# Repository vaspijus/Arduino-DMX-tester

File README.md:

DMX signal tester tool

Projekto paskirtis – daryti pirminį testavimą DMX signalais valdomiems prietaisams, bei 3pin DMX laidams. Projektą sudarys du atskiri prietaisai sudėti į vieną dėžutę.
1.	Prožektorių testavimo prietaisas skirtas patikrinti ar visi prietaiso kanalai yra veikiantys. Testavimo scenarijus: įjungus apšvietimo prožektorių bus prijungiamas  DMX testeris ir trijų mygtukų pagalba bus įvedamas pradinis prietaiso adresas (pirmas mygtukas bus skirtas šimtams ir turės vertes nuo 0 iki 5,antras mygtukas skirtas dešimtims ir turės vertes nuo 0 iki 9, trečias mygtukas skirtas vienetams turės vertes nuo 0 iki 9. Vertė padidės vienetu paspaudus mygtuką.), tuomet ketvituoju mygtuku (enter) bus paleidžiamas testavimas. Testuojami bus 4 sekantys kanalai nuo to, kuris buvi įvestas. Testeris pirmiausiai pereis per visus 4 kanalus po vieną atskirai didindamas vertes nuo 0 iki 255 paskui kanalai bus įvedami poromis taip pat nuo 0 iki 255 vertės. Toks testavimas vyks iki kol enter mygtukas bus nuspaustas dar kartą arba įvestas naujas kanalo adresas. Kanalų adresai bei dabartinė testerio būsena (On Test, On Hold) bus matoma OLED ekrane. Sistemos maitinimui bus naudojama 9V baterija, įjungimui bus naudojamas dar viengas jungiklis (mygtukas), kuris įjungs abi sistemas vienu kartu (Prožektorių testerį bei DMX laidų testerį).
Reikalingų detalių sąrašas:
Arduino UNO x1
DMX shield x1
LED screen x1
Buttons x4 
9V batery x1 (same for both testers)
9 volts battery connector x1 (same for both testers)
Switch x1 
Connecting wires 
2.	Antra projekto dalis – DMX (3pin) laidų testavimo prietaisas. Šis prietaisas testuos ar signalas praeina per DMX laidą (atskiras laido gyslas). Tam bus naudojamas vienas mygtukas, kuris įjungs/išjungs testavimą. Prijungus DMX laidą ir paleidus testavimą iš 3 digital output pinų bus siunčiami signalai į 3 digital input ir tikrinama ar signalas buvo gautas.
Testavimo logika žingsniais:
1 – patikrinamas kiekvienas pin atskirai (įjungiamas pin 1 sekundei ir pereinama prie senakčio pin taip paraktojami 3 ratai).
2 – Ijungiami visi trys pin vienu kartu 
3 – Jei kažuris iš 3 pinų signalo nepraleidžia arba du laidai yra užsitrumpinę, tuomet LED ties tuo pin`u pradeda mirgsėti iki tol kol testavimo mygtukas bus išjungtas ir paleistas iš naujo. 
Prie kiekvieno digital input ir output skirtingų spalvų LED žymės skirtingus pin numerius. 
1 pin  Green LED
2 pin  Blue LED
3 pin  Yellow LED
Šiam testavimo prietaisui bus daroma spausdintoji plokštė suri užsidės kaip shield and Arduino UNO mikrovaldiklio, žemiau išvardintos reikalingos detalės šiam prietaisui pagaminti:

Arduino Uno x1
Spausdintoji plokštė (užsidedanti kaip shield and arduino UNO) x1
Green LED x2 (SMD)
Blue LED x2 (SMD)
Yellow LED x2 (SMD)
XLR socket male x1
XLR socket female x1
Resistors x6 (1k)
9V batery x1 (same for both testers)
9 volts battery connector x1 (same for both testers)
Switch x1 (same for both testers)
Connecting wires 
-----------------------------------------------------------------------------------------
1. Usage scenario 

DMX tester tool:
1. Paspaudus prietaso jungiklį, įsijungs OLED ekranas su užrašu "Insert addr"
2. adresas bus įvedamas trimis mygtukais 
#1 - simtai (mygtuko reikšmės nuo 0 iki 5) vienas paspaudimas +1 vertė ekrane.
#2 - dešimtys (mygtuko reikšmės nuo 0 iki 9)  vienas paspaudimas +1 vertė ekrane.
#3 - vienetai (mygtuko reikšmės nuo 0 iki 9)  vienas paspaudimas +1 vertė ekrane.
Spaudžiant vieną iš trijų mygtukų vertė ekrane keisis pagal paspaudimus.
SET: #1 #2 #3
3. Surinkus norima adresą ketvirtasis mygtukas "enter" pradės testavimą. Ekrane atsiras užrašas ADDR:(adreso numeris) 
Bus testuojami 3 sekantys kanalai nuo to kanalo, kuris buvo įvestas.
4. Vėl paspaudus "enter" mygtuką testavimas bus sustabdytas. Ekrane bus rodoma -  SET:"paskutinė įvesta vertė"
5. Išungus prietaisą bet kurioje stadijoje ir vėl jį įjungus jis startuos nuo 0 adreso su užrašu "insert addr"

DMX laidų testeris:
1. Įjungus prietaisą su jungikliu visi 6 indikaciniai LED isijungs 2 sekundems. ir paskui išsijungs.
2. Nuo to momento kai gaminys įjungtas jis nuolatos kartos tris programas:
#1 - Atskirai tikrins XLR pin1, pin2, pin3 
Jei per pin1 signalas praeina LED
#2 - 
#3 -

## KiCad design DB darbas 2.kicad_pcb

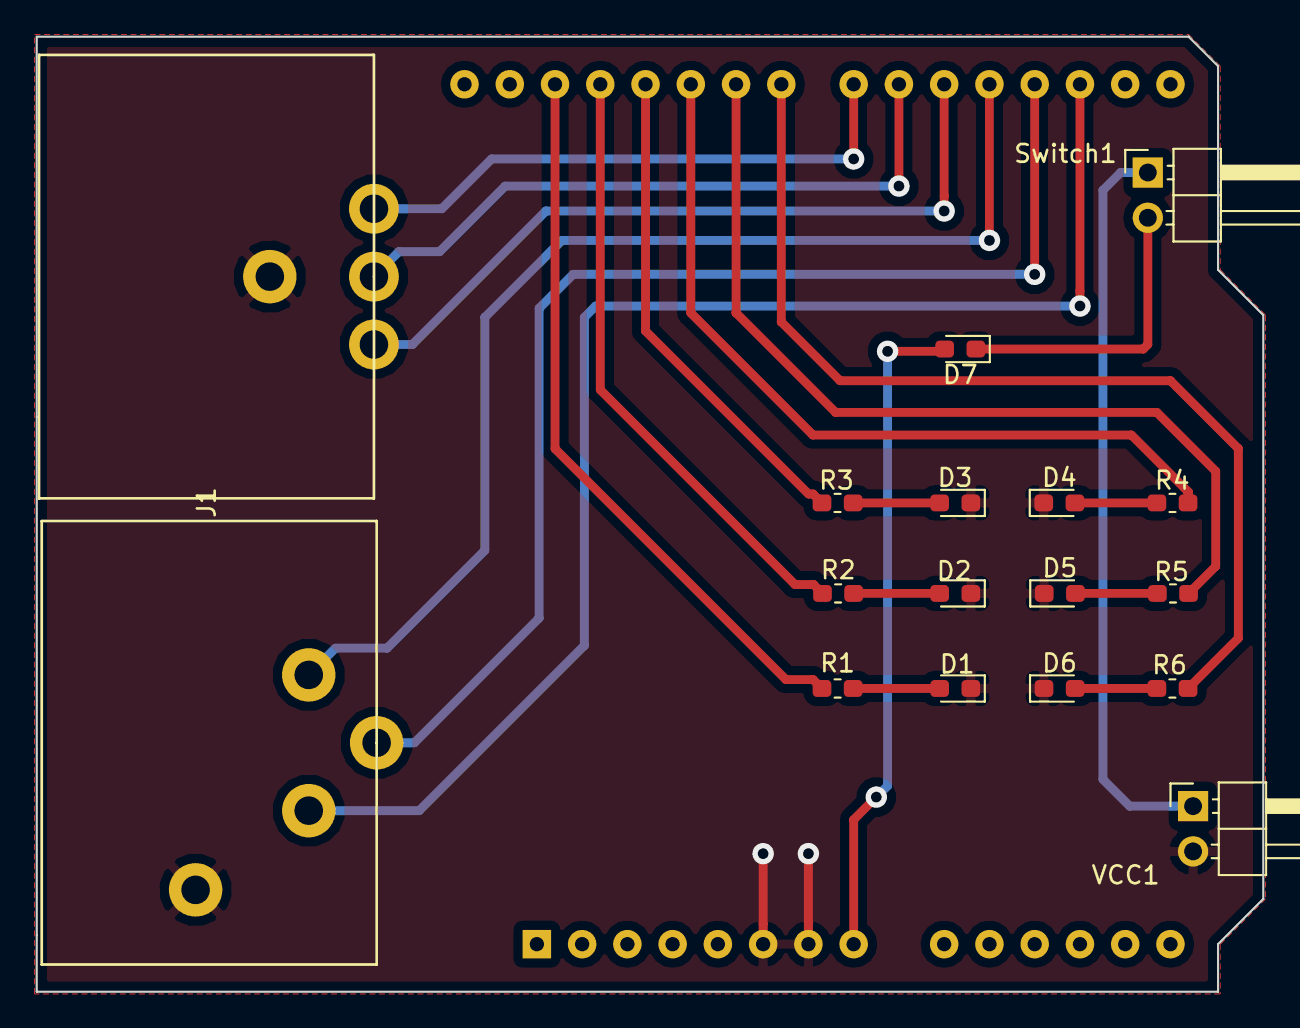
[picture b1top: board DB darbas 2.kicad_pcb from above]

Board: 2 copper layers, 68.8 x 53.6 mm, 18 parts (1 on the bottom side), 22 nets.

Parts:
D1, D2, D3, D4, D5, D6: LED; LED_0603_1608Metric_Pad1.05x0.95mm_HandSolder
D7: DIODE; D_0603_1608Metric_Pad1.05x0.95mm_HandSolder
J1, J3: XLR3_Ground; XLR_footprint
R1, R2, R3, R4, R5, R6: 300; R_0603_1608Metric_Pad1.05x0.95mm_HandSolder
Switch1: Conn_01x02_Female; PinHeader_1x02_P2.54mm_Horizontal
U1: Arduino_UNO_R2
VCC1: Connector; PinHeader_1x02_P2.54mm_Horizontal

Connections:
GND: D1.1, D2.1, D3.1, D4.1, D5.1, D6.1, J1.G, J3.G, U1.6, U1.7, VCC1.2
unnamed: D1.2, R1.2
unnamed: D2.2, R2.1
unnamed: D3.2, R3.1
unnamed: D4.2, R4.1
unnamed: D5.2, R5.1
unnamed: D6.2, R6.1
unnamed: D7.1, Switch1.2
unnamed: D7.2, U1.8
unnamed: J1.1, U1.22
unnamed: J1.2, U1.20
unnamed: J1.3, U1.21
unnamed: J3.1, U1.17
unnamed: J3.2, U1.19
unnamed: J3.3, U1.18
unnamed: R1.1, U1.28
unnamed: R2.2, U1.27
unnamed: R3.2, U1.26
unnamed: R4.2, U1.25
unnamed: R5.2, U1.24
unnamed: R6.2, U1.23
unnamed: Switch1.1, VCC1.1

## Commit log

2018-11-21 kiCAD failai
2018-11-27 DMX tester schema + Updated PCB
2018-11-27 Create DMX testrios schema 1.1 + pcb
2018-11-27 DMX laidų testeris + PCB Rev. 1.1
2018-11-30 Gerber + drill files
2018-12-01 DMX laidų testeris REV 1.2
2018-12-01 Gerber + drill files Rev. 1.2
2018-12-12 Ver1.3
2018-12-12 Gerber + drill+ Kicad Ver1.3
2018-12-14 REV 1.0
